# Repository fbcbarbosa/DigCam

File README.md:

Windows Virtual COM drivers: http://www.ftdichip.com/Drivers/CDM/CDM%20v2.10.00%20WHQL%20Certified.zip

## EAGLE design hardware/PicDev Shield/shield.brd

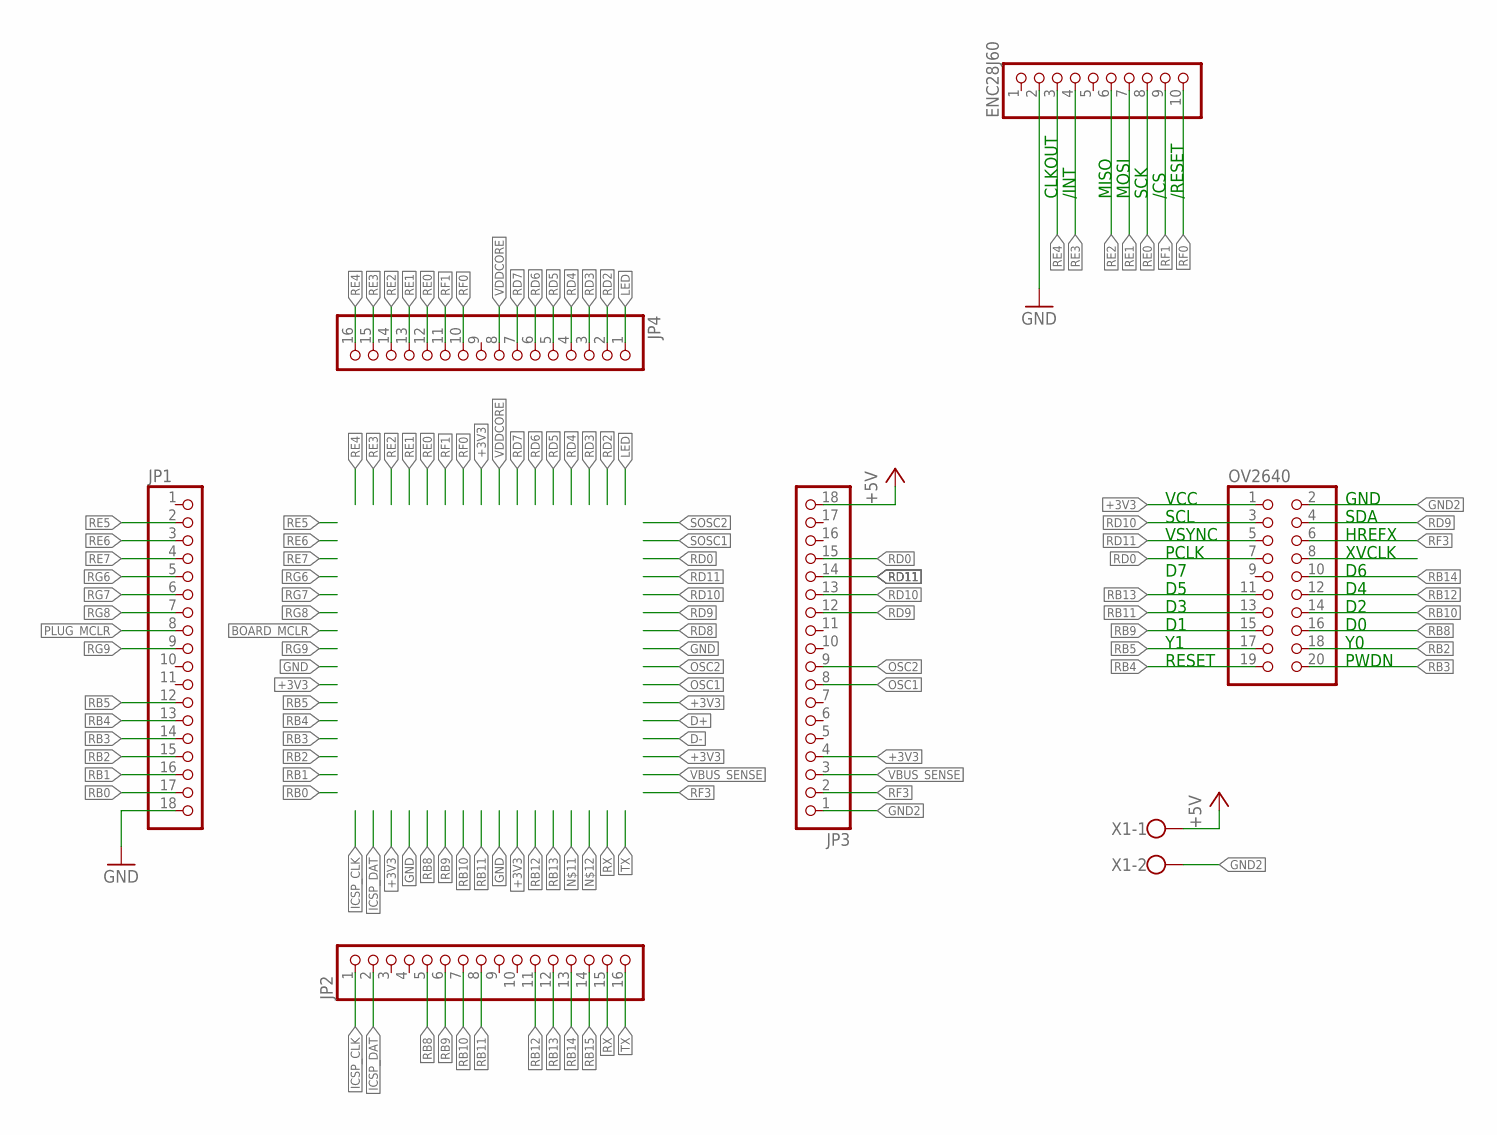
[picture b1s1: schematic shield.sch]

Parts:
ENC28J60: PINHD-1X10; 1X10
JP1, JP3: PINHD-1X18/90; 1X18/90
JP2, JP4: PINHD-1X16/90; 1X16/90
OV2640: PINHD-2X10; 2X10
X1: W237-102

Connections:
+3V3: JP3.4, OV2640.1
+5V: JP3.18, X1.1
GND: ENC28J60.2, JP1.18
GND2: JP3.1, OV2640.2, X1.2
ICSP_CLK: JP2.1
ICSP_DAT: JP2.2
LED: JP4.1
OSC1: JP3.8
OSC2: JP3.9
PLUG_MCLR: JP1.8
RB0: JP1.17, OV2640.8
RB1: JP1.16
RB2: JP1.15, OV2640.18
RB3: JP1.14, OV2640.20
RB4: JP1.13, OV2640.19
RB5: JP1.12, OV2640.17
RB8: JP2.5, OV2640.16
RB9: JP2.6, OV2640.15
RB10: JP2.7, OV2640.14
RB11: JP2.8, OV2640.13
RB12: JP2.11, OV2640.12
RB13: JP2.12, OV2640.11
RB14: JP2.13, OV2640.10
RB15: JP2.14
RD0: JP3.15, OV2640.7
RD2: JP4.2
RD3: JP4.3
RD4: JP4.4
RD5: JP4.5
RD6: JP4.6
RD7: JP4.7
RD9: JP3.12, OV2640.4
RD10: JP3.13, OV2640.3
RD11: JP3.14, OV2640.5
RE0: ENC28J60.8, JP4.12
RE1: ENC28J60.7, JP4.13
RE2: ENC28J60.6, JP4.14
RE3: ENC28J60.4, JP4.15
RE4: ENC28J60.3, JP4.16
RE5: JP1.2
RE6: JP1.3
RE7: JP1.4
RF0: ENC28J60.10, JP4.10
RF1: ENC28J60.9, JP4.11
RF3: JP3.2, OV2640.6
RG6: JP1.5
RG7: JP1.6
RG8: JP1.7
RG9: JP1.9
RX: JP2.15
TX: JP2.16
VDDCORE: JP4.8

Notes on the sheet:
CLKOUT
/INT
MISO
MOSI
SCK
/CS
/RESET
VCC
GND
SDA
HREFX
XVCLK
PWDN
SCL
VSYNC
PCLK
RESET

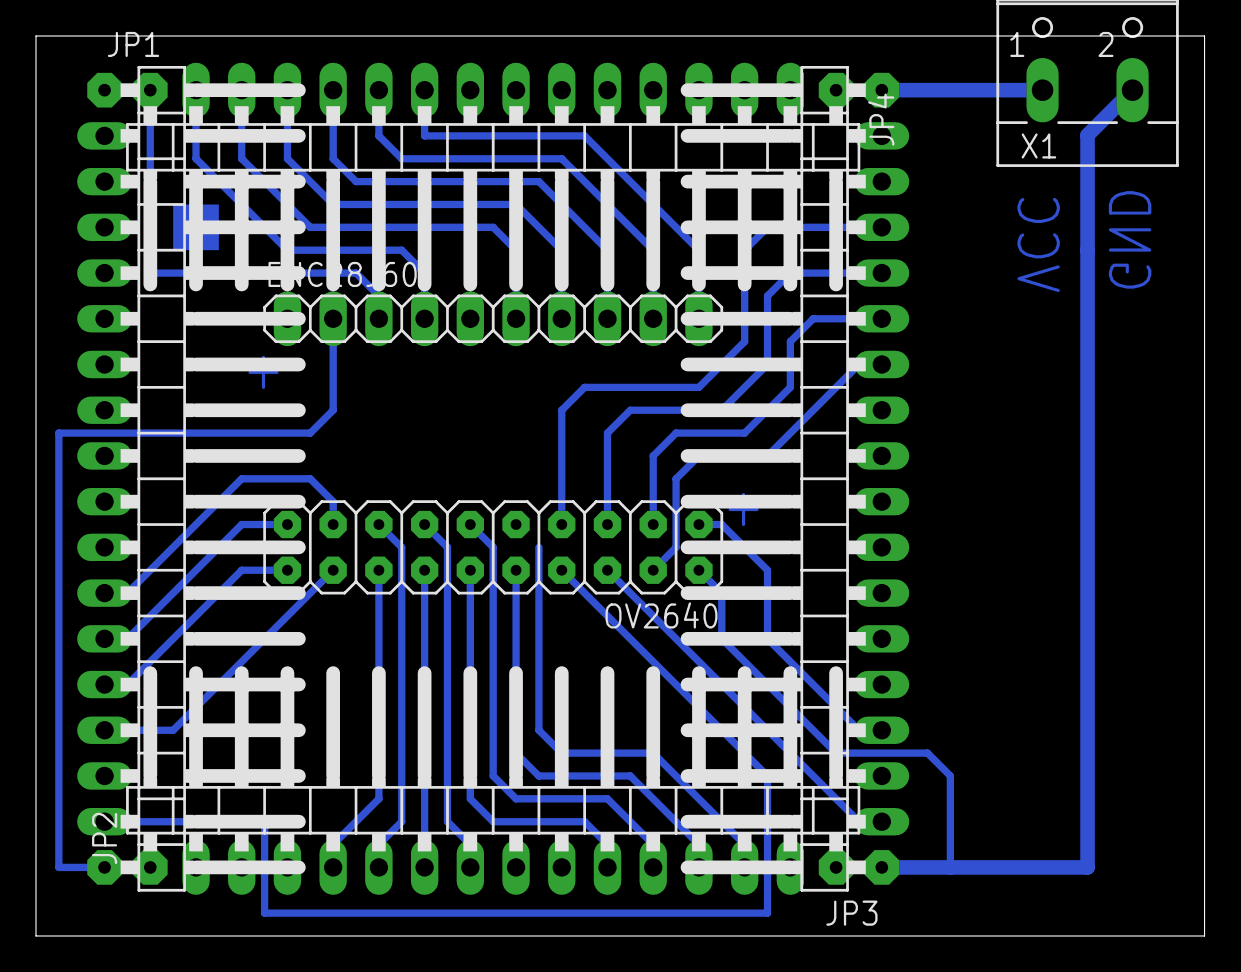
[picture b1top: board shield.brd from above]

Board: 2 copper layers, 64.9 x 50.0 mm, 7 parts (0 on the bottom side), 28 nets.

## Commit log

2014-04-20 Changed names and some basic MPLABX Project setup
2014-04-20 Changed project name + some basic MPLAB setup
2014-04-25 Added UART functions to project. Still needs testing.
2014-04-29 Further changes to UART
2014-05-09 Large update to UART functions + SCILAB code to read serial data from usb port.
2014-05-09 Scilab program now allows users to write into serial port!
2014-05-10 Changed Scilab for Python, command implementation
2014-05-13 Implementation of a instruction database in Python
2014-05-19 Exception Handling
2014-06-05 Terminal instructions, better organization, etc.
2014-06-08 Finished shield
2014-06-09 Added Delay function prototype!
2014-06-09 A LOT O STUFF
2014-06-16 Completed skeleton of i2c_cam and ov2640 functions
2014-06-21 I2C config/new camera functions/extra debugging functions/terminal update - I2C does not work atm, but camera can be activated/deactivated.
2014-06-24 Corrected camera address. SCCB is working.
2014-06-24 Added proto-photo function.
2014-06-30 IT WORKS!
2014-07-04 Works with YUV422. Testing JPEG. Needs to adjust Window Size.
2014-07-05 YUV422 400x200
    YUV422
2014-07-05 working
    working
2014-07-05 --
    --
2014-07-05 Comi demais galera
    Comi demais galera
2014-07-05 Clean-up
    clean-up
2014-07-06 FINAL
    FINAL
2014-07-24 Beta
    Beta
